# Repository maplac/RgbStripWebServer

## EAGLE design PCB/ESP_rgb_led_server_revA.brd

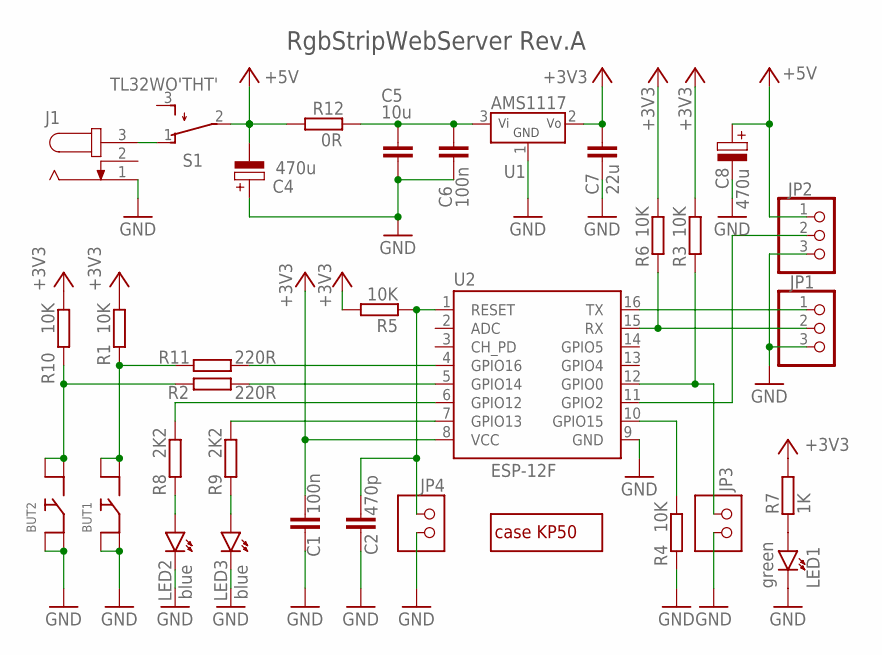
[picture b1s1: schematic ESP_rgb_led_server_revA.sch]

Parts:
BUT1, BUT2: BUTTON'SMD'; BUTTON_SMD
C1, C6: 100n; C0805
C2: 470p; C0805
C4, C8: 470u; ELYT-10MM/90
C5: 10u; C0805
C7: 22u; C0805
J1: JACK-PLUG1; SPC4078
JP1, JP2: PINHD-3X1
JP3, JP4: PINHD-2X1
LED1: green; LED3MM
LED2, LED3: blue; LED3MM
R1, R3, R4, R5, R6, R10: 10K; R0805
R2, R11: 220R; R0805
R7: 1K; R0805
R8, R9: 2K2; R0805
R12: 0R; R0805
S1: TL32WO'THT'; TL3XWO
U1: AMS1117; SOT223
U2: ESP-12F; ESP-12F-ADAPTER
U$1: CASE-KP50; KP50-CASE

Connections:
+3V3: C1.2, C7.2, R1.2, R3.2, R5.2, R6.2, R7.2, R10.2, U1.2 (VOUT), U2.8 (VCC)
+5V: C4.N (NEG), C8.P (POS), JP2.1, R12.2, S1.2
GND: BUT1.1 (4), BUT1.2, BUT2.1 (4), BUT2.2, C1.1, C2.1, C4.P (POS), C5.1, C6.1, C7.1, C8.N (NEG), J1.1, JP1.3, JP2.3, JP3.2, JP4.2, LED1.K, LED2.K, LED3.K, R4.1, U1.1 (GND), U2.9 (GND)
unnamed: JP1.1, U2.16 (TX)
unnamed: JP3.1, R3.1, U2.12 (GPIO0)
unnamed: C2.2, JP4.1, R5.1, U2.1 (RESET)
unnamed: R4.2, U2.10 (GPIO15)
unnamed: JP1.2, R6.1, U2.15 (RX)
unnamed: JP2.2, U2.11 (GPIO2)
unnamed: J1.3, S1.1 (O)
unnamed: R11.2, U2.4 (GPIO16)
unnamed: LED1.A, R7.1
unnamed: R2.2, U2.5 (GPIO14)
unnamed: R8.2, U2.6 (GPIO12)
unnamed: LED2.A, R8.1
unnamed: R9.2, U2.7 (GPIO13)
unnamed: LED3.A, R9.1
unnamed: BUT2.3 (1), BUT2.4 (3), R2.1, R10.1
unnamed: C5.2, C6.2, R12.1, U1.3 (VIN)
unnamed: BUT1.3 (1), BUT1.4 (3), R1.1, R11.1

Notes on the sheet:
RgbStripWebServer Rev.A

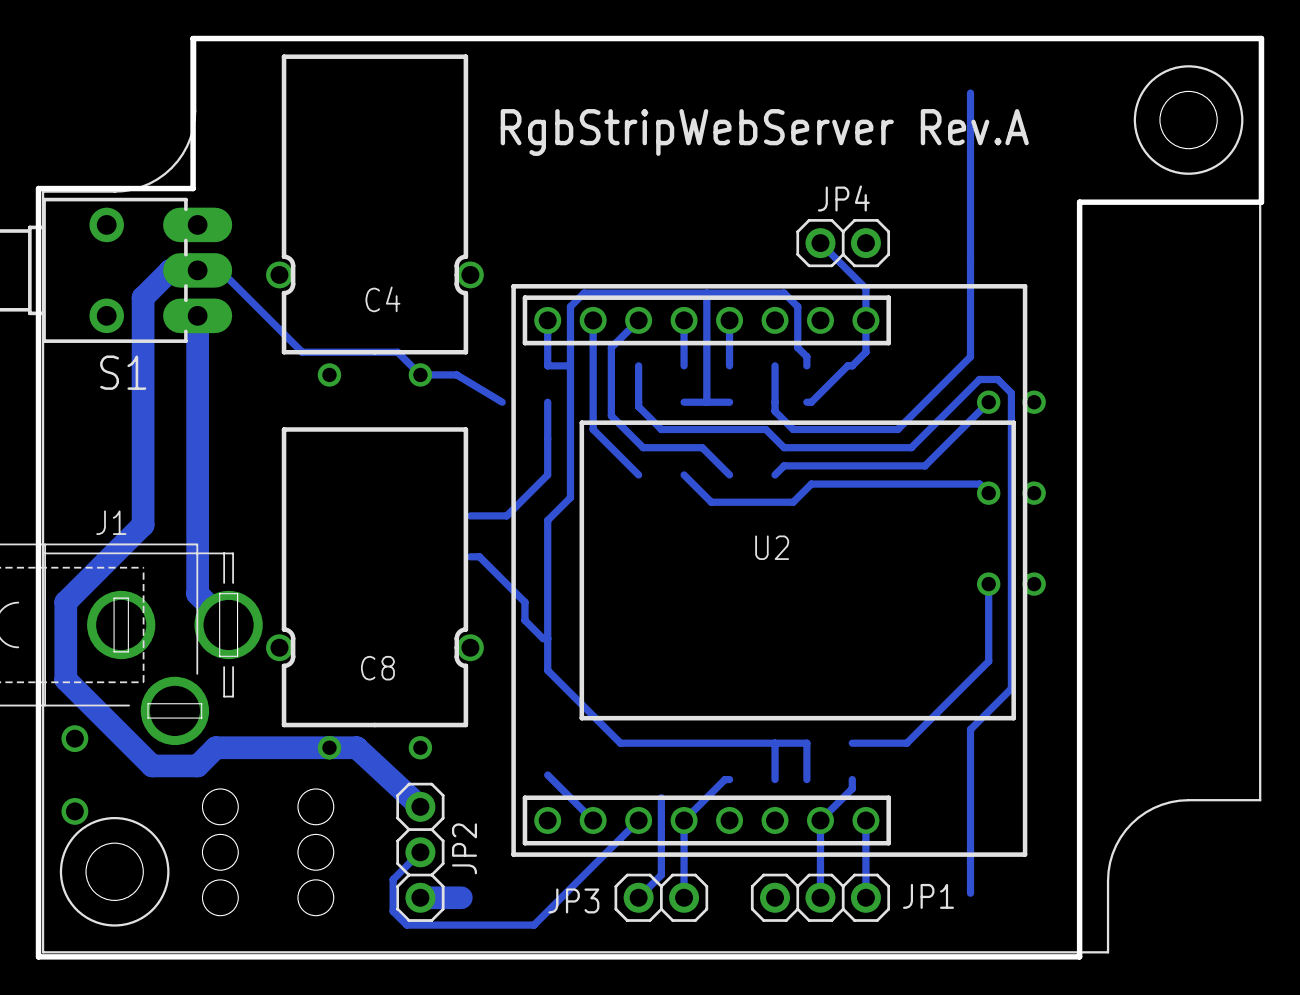
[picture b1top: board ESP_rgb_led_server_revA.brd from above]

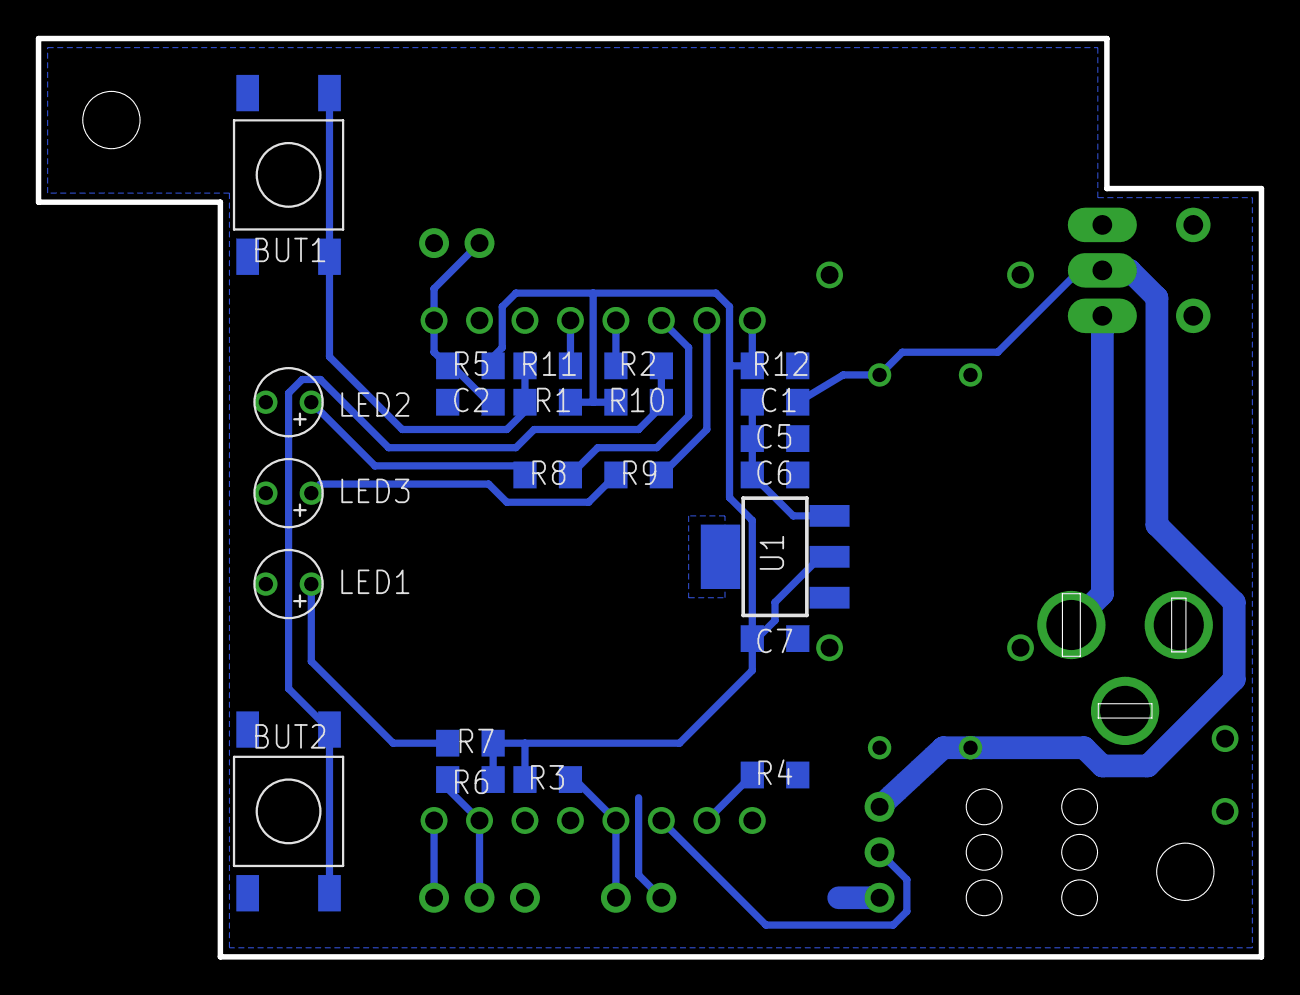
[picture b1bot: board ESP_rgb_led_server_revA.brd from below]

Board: 2 copper layers, 68.3 x 51.3 mm, 33 parts (23 on the bottom side), 20 nets.

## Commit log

2017-05-07 :octocat: Added .gitattributes & .gitignore files
2017-05-07 added: firmware for ESP8266
2017-05-07 added: lua scripts
2017-05-07 added: web files
2017-05-07 added: schematics and PCB layout
2017-05-15 added: schematics and layout exported as images
2017-05-18 added: photos
2017-06-13 fixed #1: timers for random color effect are correctly stopped
2017-06-13 changed: random color effect changes colors separately in bottom and top half
2017-06-15 modified: improved randomness of random color effect
2017-06-18 added: random color effect can show different color in top and bottom half
2017-06-18 resolved #6: added 5 more saved colors to static color effect
2017-06-19 modified: button debounce timers
2017-06-19 resolved #3: modified css files to make the interface more colorful
2017-06-21 added: support for caching in web browser
2017-06-21 added: screenshots of web interface
2017-06-24 changed: significantly better heap memory management
2017-12-22 fixed: default settings
2017-12-22 modified: commented debug prints
